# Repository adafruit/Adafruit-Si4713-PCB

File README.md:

# Adafruit Si4713 FM Transmitter Breakout PCB
<a href="http://www.adafruit.com/products/1958"><br/>
Click here to purchase one from the Adafruit shop</a>

Become your very own pirate radio station with this FM radio transmitter. This breakout board, based on the best-of-class Si4713, is an all-in-one stereo audio FM transmitter that can also transmit RDS/RBDS data!

Wire up to your favorite microcontroller (we suggest an Arduino) to the I2C data lines to set the transmit frequency and play line-level audio into the stereo headphone jack. Boom! Now you are the media. Listen using any FM receiver such as your car or pocket radio receiver - this is an easy way to transmit audio up to about 10 meters / 30 feet away.

PCB files for Adafruit Si4713 FM Transmitter Breakout. The format is EagleCAD schematic and board layout
- https://www.adafruit.com/product/1958

### License

Adafruit invests time and resources providing this open source design, please support Adafruit and open-source hardware by purchasing products from [Adafruit](https://www.adafruit.com)!

All text above must be included in any redistribution

Designed by Limor Fried/Ladyada for Adafruit Industries.
Creative Commons Attribution/Share-Alike, all text above must be included in any redistribution. 
See license.txt for additional information.

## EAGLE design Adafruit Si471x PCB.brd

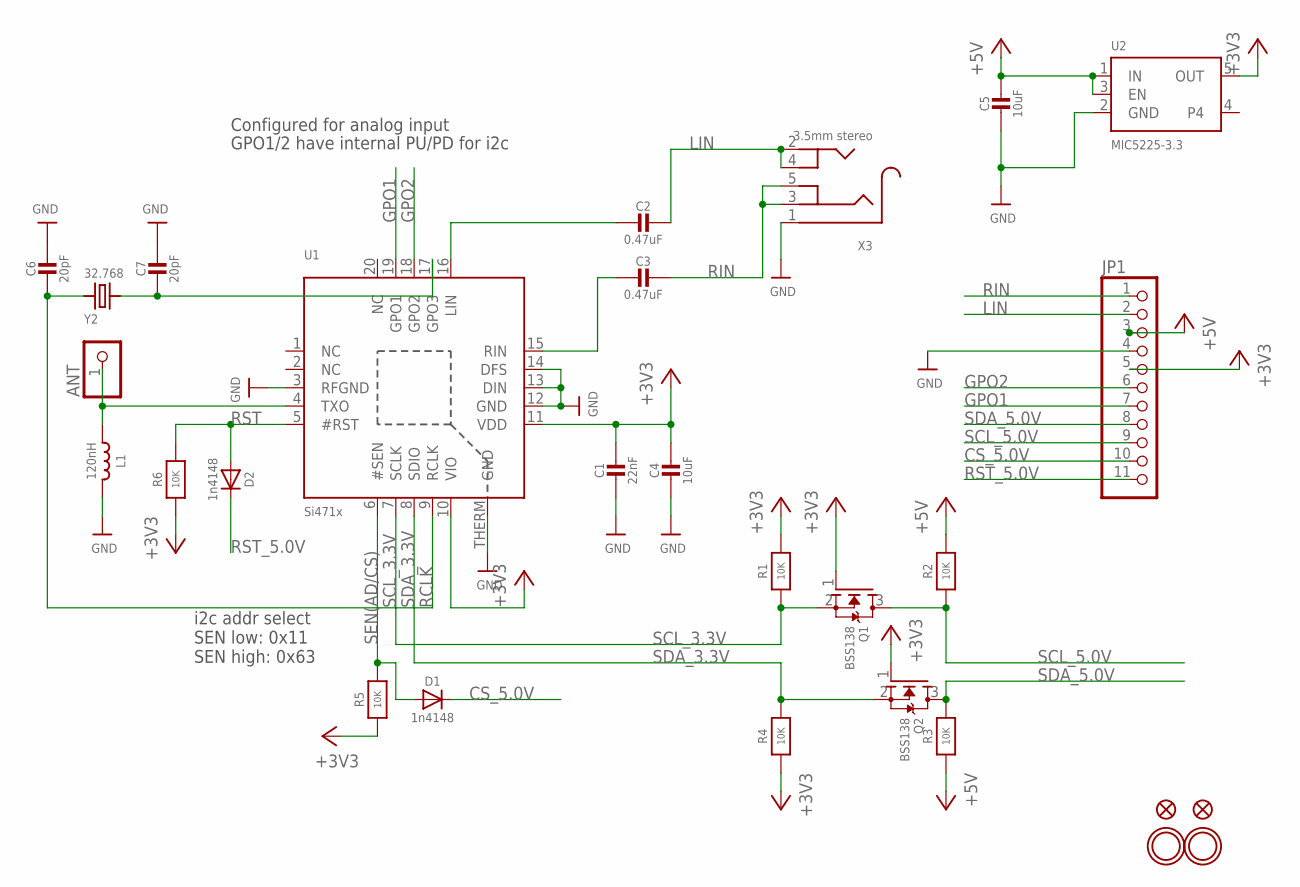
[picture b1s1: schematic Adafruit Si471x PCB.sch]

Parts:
ANT: PINHD-1X1; 1X01
C1: 22nF; 0805-NO
C2, C3: 0.47uF; 0805-NO
C4, C5: 10uF; 0805-NO
C6, C7: 20pF; 0805-NO
D1, D2: 1n4148; SOD-323
FID1, FID2: FIDUCIAL""; FIDUCIAL_1MM
JP1: HEADER-1X11; 1X11_ROUND
L1: 120nH; _0805
Q1, Q2: BSS138; SOT23
R1, R3, R5, R6: 10K; 0805-NO
R2, R4: 10K; _0805MP
U1: Si471x; SI471X
U2: MIC5225-3.3; SOT23-5
U$15, U$17: MOUNTINGHOLE2.5; MOUNTINGHOLE_2.5_PLATED
X3: 3.5mm stereo; 4UCONN_19269
Y2: 32.768; CRYSTAL_8X3.8

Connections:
+3V3: C1.1, C4.1, JP1.5, Q1.1 (G), Q2.1 (G), R1.2, R4.1, R5.1, R6.1, U1.10 (VIO), U1.11 (VDD), U2.5 (OUT)
+5V: C5.1, JP1.3, R2.2, R3.1, U2.1 (IN), U2.3 (EN)
CS_5.0V: D1.C, JP1.10
GND: C1.2, C4.2, C5.2, C6.1, C7.1, JP1.4, L1.2, U1.3 (RFGND), U1.12 (GND), U1.13 (DIN), U1.14 (DFS), U1.THERM (GND), U2.2 (GND), X3.1
GPO1: JP1.7, U1.19 (GPO1)
GPO2: JP1.6, U1.18 (GPO2)
LIN: C2.1, JP1.2, X3.2, X3.4
unnamed: ANT.1, L1.1, U1.4 (TXO)
unnamed: C2.2, U1.16 (LIN)
unnamed: C3.2, U1.15 (RIN)
unnamed: C7.2, U1.17 (GPO3), Y2.P$4 (2)
RCLK: C6.2, U1.9 (RCLK), Y2.P$1 (1)
RIN: C3.1, JP1.1, X3.3, X3.5
RST: D2.A, R6.2, U1.5 (#RST)
RST_5.0V: D2.C, JP1.11
SCL_3.3V: Q1.2 (S), R1.1, U1.7 (SCLK)
SCL_5.0V: JP1.9, Q1.3 (D), R2.1
SDA_3.3V: Q2.2 (S), R4.2, U1.8 (SDIO)
SDA_5.0V: JP1.8, Q2.3 (D), R3.2
SEN(AD/CS): D1.A, R5.2, U1.6 (#SEN)

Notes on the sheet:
Configured for analog input
GPO1/2 have internal PU/PD for i2c
i2c addr select SEN low: 0x11 SEN high: 0x63

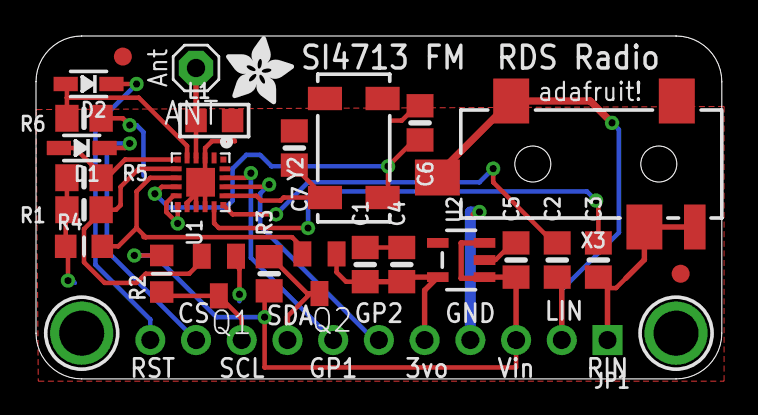
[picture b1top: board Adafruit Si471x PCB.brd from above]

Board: 2 copper layers, 38.1 x 19.1 mm, 30 parts (1 on the bottom side), 20 nets.

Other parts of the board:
U$7: ADAFRUIT_3.5MM
U$9: ADAFRUIT_TEXT_20MM

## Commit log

2015-03-02 init

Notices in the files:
parts and their libraries:
microbuilder: This work is placed in the public domain, and may be freely used for commercial and non-commercial work with the following conditions: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
